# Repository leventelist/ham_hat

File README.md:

# Raspberry PI hat for radio amateurs

## History

I've been doing a lot of SOTA activations with Raspberry PI like SBCs, and there
where always issues, like RF interference, and power supply shorts. I started to
add things like galvanically decoupled audio interface, a step down power supply. It
was working, but it looked like a mess.

This piece of hardware integrates all needed equipment in one nice hat. It is designed
to put the RPI in a metallic box to further isolate from RF signals.

It was designed using [KiCad](https://www.kicad.org/).

## Applications

* HF/VHF digital modes (PSK, FT8, etc)
* HF/VHF AX.25 based modes (Packet, APRS, etc)
* CW keying
* Clock synchronization
* Position tracking

## Features

 * 3A power supply with wide input voltage range: 8 to 35V
 * Ublox MAX-8/10 GPS receiver for position and time synchronization
 * Inductive audio couplers to minimize GND loops. Up to 4kHz.
 * PWM controlled cooling fan
 * GPIO controlled PTT from the PI
 * GPIO controlled CW key from the PI
 * RTC
 * Shutdown button
 * Run LED

GPS antenna is not integrated in the device, so an external antenna connector is
mounted on the PCB.

Ufortunately, the sound card of the PI can not record audio, so an
external sound card must be used. I use
[this](https://www.axagon.eu/en/produkty/ada-17) particular device with good
results. I usually break the plastic housing, and solder a shielded cable
directly to the audio interface (J109).

The GPS is needed for APRS and time synchronization. There is an onbard RTC to have some redundancy.

## Placing variants

There are a few components that mounted or unmounted depending on particular application.

### HT radio

When this device is used with a handheld radio, that has a PTT and mic input (Like the FT-4X), mount C108 and R116. Please note that the value of R116 might vary based on the actual transceiver used.

If used with a radio that has separate input for audio and PTT, mount a 0 Ohm resistor to C108. You might also leave C108 as a capacitor (22uF), but it is not really needed.

C108 and R116 is placed on the layout that it can be mounted or replaced after everything else is mounted too. All you need is the dismount tha cooling fan.

### High bandwidth audio

If you want to have direct access to the audio interface of your radio, you can leave T101 and T102 unpopulated and short JP102 and JP103, JP104. Please note that you will loose GND separation as well.

## Mechanics

It is designed to fit on the Raspberry PI 4. Be aware, that if the heatsink on the CPU is too high, it might
conflict with the screws of the fan. If that happens, mount the heatsink 45 degrees.

### Box

A box is designed in FreeCAD using sheets of PCB. The idea is to use bare, one sided PCBs, and solder the plates from the inside. The sheets can be easily milled by a CNC machine.

There are several cutouts on the box.

In the front, you have the power inlet, and a second cutout for powering the attached LCD screen. On the right side of the front sheet, there is a cutout for the power chord to the GPS antenna, if needed.

On the right, there are anouther cutout for the audio cable.

The assembly does not include some (all) the models, hence they might violate copyright.

## Connection to the radio

The hat comes with a DB9 connector to connect up your rig. I wanted to have a screw lock
connector, and this was the best choice. The pin out looks like this.

| Signal name | Pin of the DB9 | Comment                  |
|-------------|----------------|--------------------------|
| TX audio    | 1              | Audio input of your rig  |
| KEY         | 2              | CW key of the rig        |
| PTT         | 3              | PTT input of your rig    |
| NC          | 4              | Not connected            |
| RX audio    | 5              | Audio output of your rig |
| GND         | 6              | Audio ground             |
| GND         | 7              | Audio ground             |
| GND         | 8              | Audio ground             |
| GND         | 9              | Audio ground             |

### GPIO connections

| Signal name | GPIO | Commnet |
|-------------|------|---------|
| PTT         | 12   |         |
| KEY         | 21   |         |
| DCD         | 16   |         |

## Connection to the soundcard

J105 provides connection to the soundcard.

| Signal name | Pin of J105            | Comment                          |
|-------------|------------------------|----------------------------------|
| RX audio    | 1                      | Mic input of your soundcard      |
| TX audio    | 4                      | Speaker output of your soundcard |
| GND         | 2,3                    | Audio ground                     |

## Power connection

J101 provides power connection. The maximum input voltage is 35Volts.

## GPS

Use u-blox MAX-8C/Q or MAX-M10S GNSS module. When the MAX-10 is used, don't populate R113.

Connect your passive or active GPS antenna to J104. Use 3.3V active antenna. PPS signal is provided on GPIO18.

When passive antenna is used, don't populate L102.

[Here](https://austinsnerdythings.com/2021/04/19/microsecond-accurate-ntp-with-a-raspberry-pi-and-pps-gps/) is an excellent article how to set up GPIO-PPS for ntpd.

## RTC

BQ32000 based precision RTC is provided for backup if the GPS can't provide accurate timing.

### Enable I²C on Raspberry Pi
```bash
sudo raspi-config
```
Navigate to:
```
Interfacing Options → I2C → Enable
```
Reboot the Raspberry Pi:
```bash
sudo reboot
```

### Check I²C Communication
```bash
sudo apt install i2c-tools
i2cdetect -y 1
```
You should see the RTC at **0x68**.

### Configure Linux to Use BQ32000
```bash
sudo modprobe rtc-bq32k
echo bq32000 0x68 | sudo tee /sys/class/i2c-dev/i2c-1/device/new_device

# This next one line only needed to set initial time of the RTC
# Otherwise it'll fail to read
sudo hwclock -w

# Test to read the RTC
sudo hwclock -r
```

### Make It Persistent
Edit `/boot/firmware/config.txt`:

Add the following line:
```
dtoverlay=i2c-rtc,bq32000
```
Save and reboot:
```bash
sudo reboot
```

### Disable Fake RTC (if needed)
```bash
sudo systemctl disable fake-hwclock
sudo systemctl stop fake-hwclock
```
Edit `/lib/udev/hwclock-set` and comment out:
```bash
#if [ -e /run/systemd/system ] ; then
#    exit 0
#fi
```
```bash
apt remove fake-hwclock
```

### Create a systemd service to set system clock from RTC

/etc/systemd/system/rtc-sync.service

The content of this file attached.

### Sync RTC with System Time
Set RTC from system time:
```bash
sudo hwclock -w
```
Set system time from RTC:
```bash
sudo hwclock -s
```

### Final Test
Check that the RTC retains the time after reboot:
```bash
sudo hwclock -r
```

Connect a 3V battery to BT101 for offline RTC operation.

## FAN control

PWM shall be enabled on GPIO13.

If you don't want PWM control, short JP101, and the fan will spin at full power all times.

There's a non-PWM control of the fan that works out of the box using the Raspberry PI OS.

Open raspi-config, under Performance Options, you shall select the desired temperature,
and the GPIO pin which is 13.

## Shutdown button can be connected to J106

To make it work, you have to add these lines to /boot/firmware/config,txt

```
dtoverlay=gpio-shutdown,gpio_pin=26
```

Ther's also a LED (D107 )that shines when the system is running. When it
Doesn't, it is safe to remove power from the RPI.

To make this work, add this too:

```
dtoverlay=gpio-poweroff,gpiopin=7,active_low=1
```

## Accessories

These items needed for the hat for full functionality.

All sourced from [Farnell](https://www.farnell.com/), unless othervise noted. (Sorry, I'm Hungary based.)

| Item | Source designator        | Comment |
|--------------------|------------|---------|
| RTC Battery        | 1892670    | The idea is to use heatshrink tube and some wires. |
| RTC Battery holder | 3583203    | External battery holder for CR2032 |
| Heatsink           | 1211701 or https://www.alza.hu/raspberry-pi-rb-hutoborda-d4147799.htm?o=21 ||
| Standoff           | 1466844 | It must be 12mm in length |
| Mounting screws M2.5x6 | | |
| GPS antenna        | [This](https://www.soselectronic.hu/products/2j/2j431gmp-250rg174-c20n-173902) or [this](https://www.soselectronic.hu/products/2j/2j0801b-c814g-217598) | Use 3V active antenna |
| RPI4 | 3369503 (8GB) or 3051887 (4GB) | |
| USB audio interface| [Alza](https://www.alza.hu/axagon-ada-10-mini-d1470921.htm) | Any other do the job. Check Linux driver availability. |
| Monitor| [Ebay](https://www.ebay.com/itm/353758771148?_trkparms=ispr%3D1&hash=item525daa77cc:g:jNQAAOSwnmlhhkpn&amdata=enc%3AAQAGAAACoPYe5NmHp%252B2JMhMi7yxGiTJkPrKr5t53CooMSQt2orsSd0ReTLyM7cxPnI6zs468EDJJHdbu7%252F6aAGgDwzooo3WFCnsE6WY2NN3WIFz%252BU3j%252B6nlMSYOqthKl8%252BB0CNXkHJGfWJwzf20ZY2tdDWUhthRak%252B0O%252FHuC9ltiij5XgROuZ1Yt7ahYbZ19ddFFTaniueENCnYQ1aBhlktfzWv7xNvLbyiVUMCgdXy2uwy0Qm1PC1w8PtdFCrKUjBzWedhAdATUyusA%252BLFfS8lKdAnUeEkUiXBHqDyRACtOih8HyopSoYK%252BuetmxNqJMW1yetVzEuVG55kdREQp8NK3DiaAyJ3VxZ2eCQS7MBWAslEs%252BcjPr5pLBJmvXicOdQsxG78lY3RixTMapBEXkMyMhr8CZ%252B%252BUgXa6K6nssZMYzkzb8xh6HKPf1HGRgakrkSU8iv0Jb0qSPHQQbUU%252BDDCgloGfOgyy3KP%252FVC8YO8aAXQEpuWYDxkgLVD9bG29n%252FxRT5bK91LAbViZxXBj7t3CMtKnw2FXJZp9tf8PF83bIWHzxw3%252FWPs3Q16F6D8dQrHa7%252FQKrBkX9ECfOG3J8w%252BXIaV0JdErB2c39fbNJsezMG0qO7EeJPmYWaZ4isKdigC4pZBSkcRq6YpXnZEsE%252FZbSkspYbLs5C%252F9QS17yAUWT6I9ebc9k7iy9tjIt2p2E%252F8tQXl7IEDUfLabC98laQ883Xs2%252BFUGj8w%252B%252FzyhRREPPlbA7segxjevzekGn9GUOD6kM6yCYgyqf3eMCqXgKofQIa6dmLZviddtP9L0a4A2mYfWhoSsyY%252FoBn6oAKnoTd9ymHzWRMWE5W5Act9JD6YpZT0wU8zPgG6x9%252BwGaIeGsotEsk1Bm2ccUKsKW1YO18BFmLPTsdw%253D%253D%7Cclp%3A2334524%7Ctkp%3ABFBM_P_ZwrNf)
| Keyboard | https://www.pcland.hu/genius-luxemate-100-usb-fekete-hun-billentyuzet-31300725113 | Any USB Keyboard. I use the one without keypad, for its compact size. |
| Mice | | Any USB, or BLE mice |
| SD card with Raspbian image. | | |
| uHDMI to HDMI cable | [Alza](https://www.alza.hu/vention-micro-hdmi-to-hdmi-cable-2m-black-d5891200.htm?o=1) | |
| DB9 Male connector | | To connect to your radio |
| Data connector for your radio |
| Shielded audio cable | | To connect the soundcard to the hat, and for the DB9 connector |

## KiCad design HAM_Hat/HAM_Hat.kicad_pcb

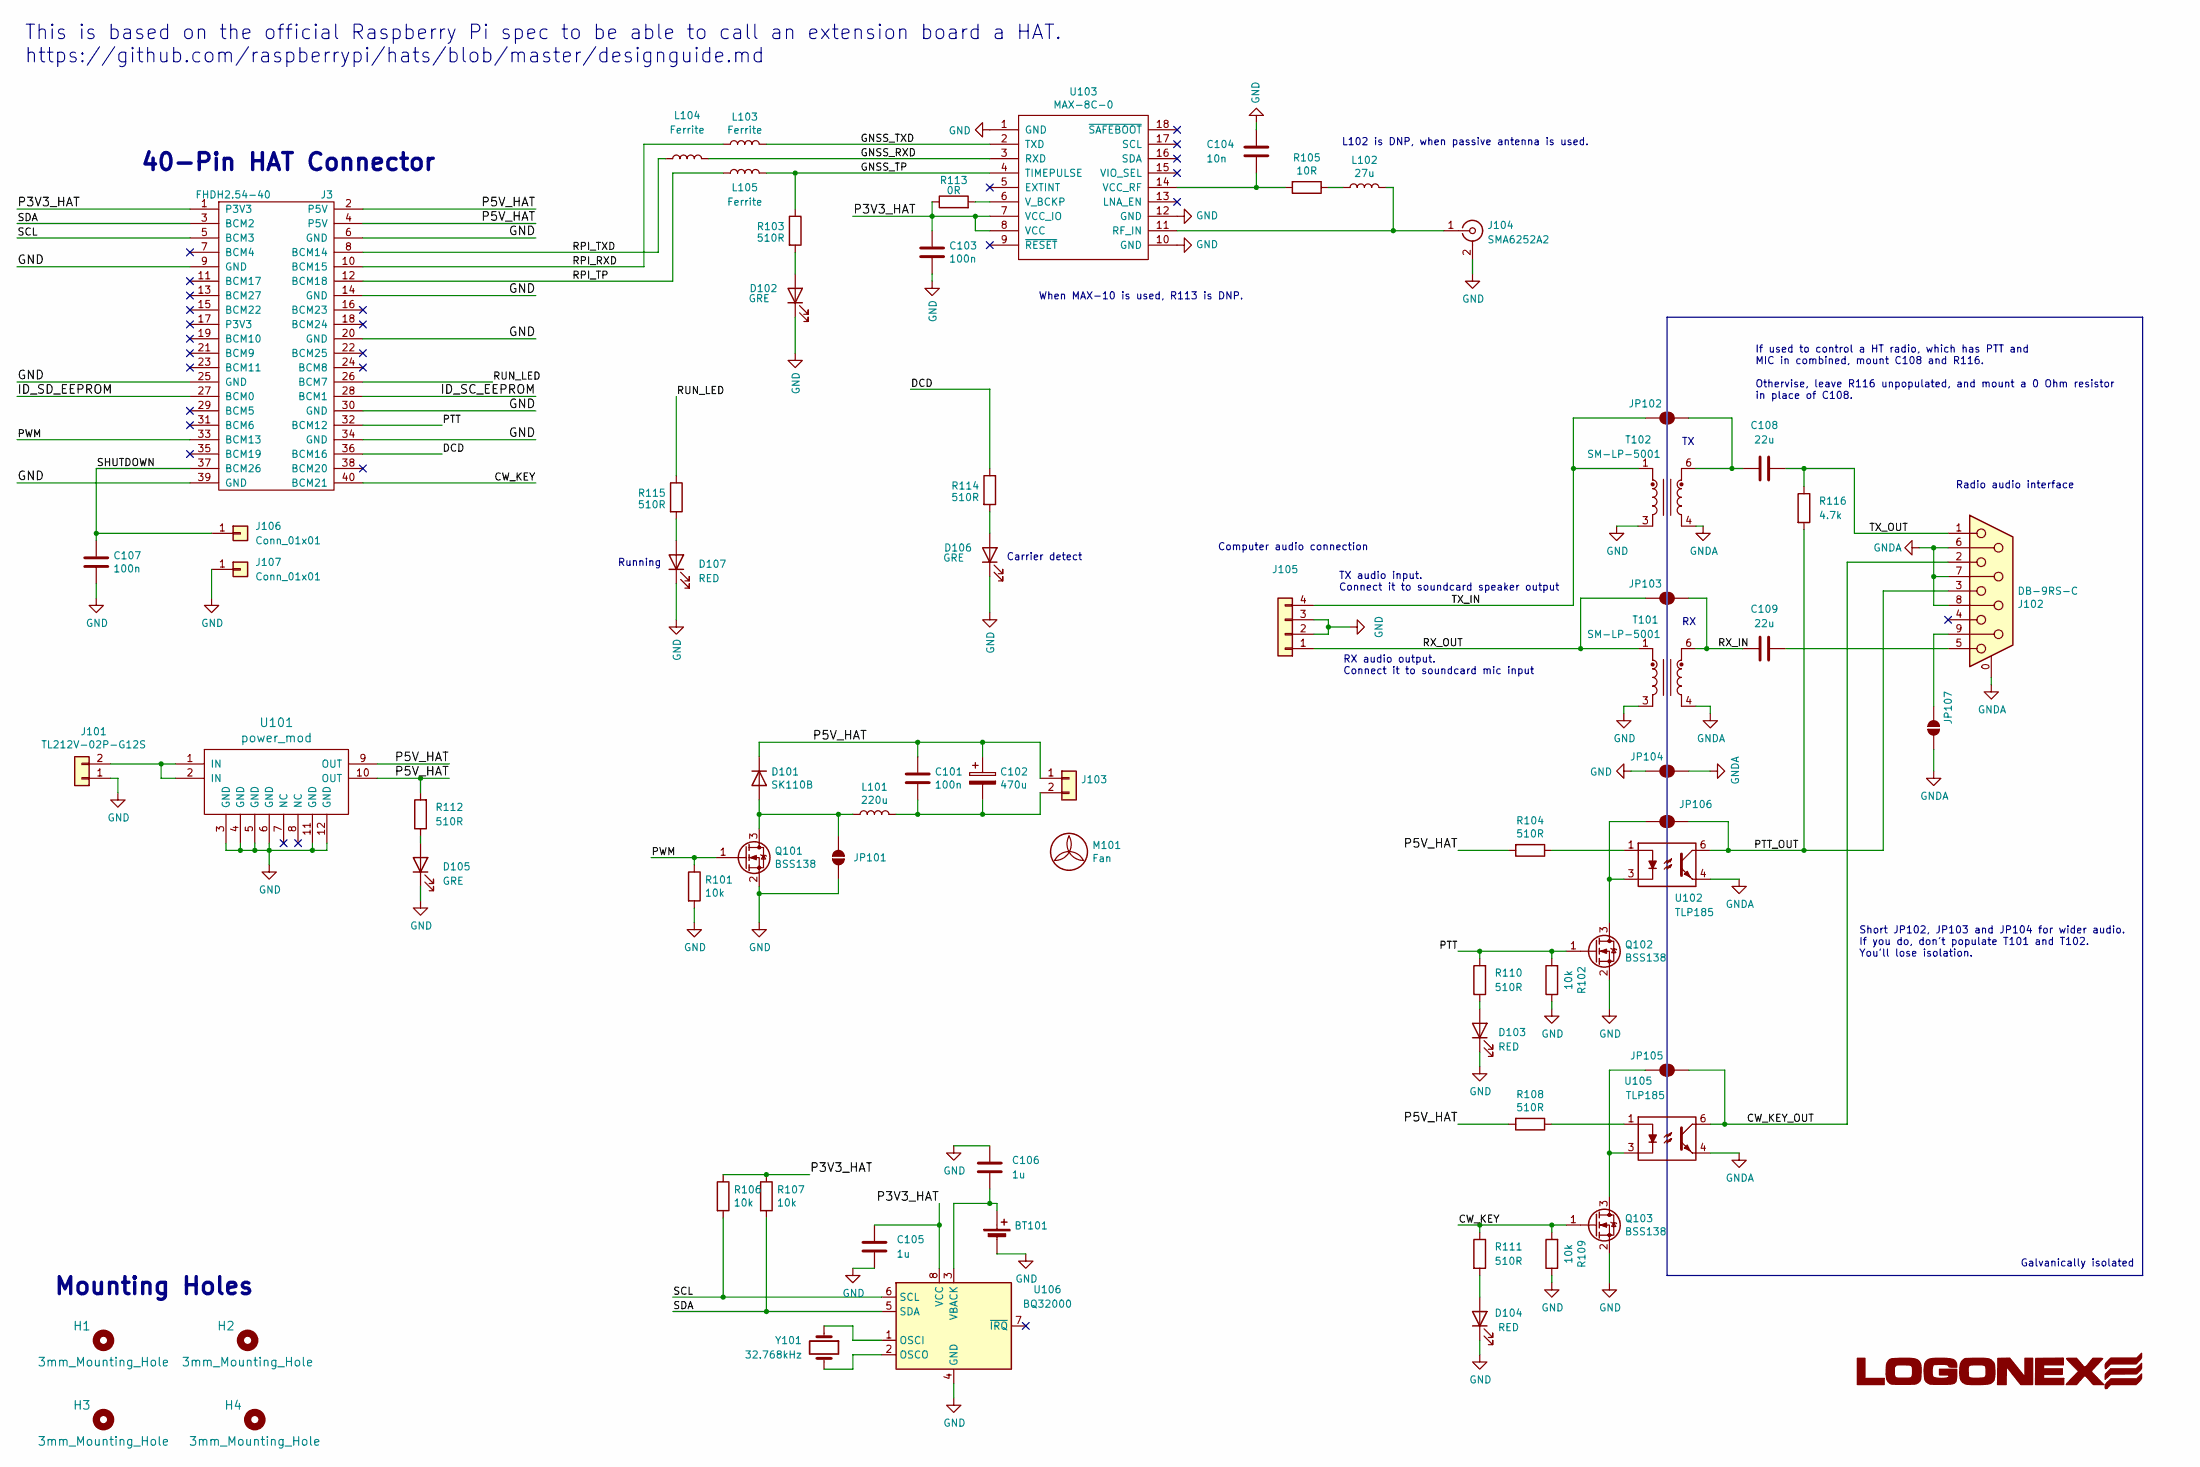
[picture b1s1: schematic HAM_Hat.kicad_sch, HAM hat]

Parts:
BT101: PinHeader_2x01_P2.54mm_Vertical
C101, C103, C107: 100n; C_0603_1608Metric
C102: 470u; CP_Radial_D10.0mm_P5.00mm
C104: 10n; C_0603_1608Metric
C105, C106: 1u; C_0603_1608Metric
C108, C109: 22u; C_1206_3216Metric
D101: SK110B; D_SMB
D102, D105, D106: GRE; LED_0603_1608Metric
D103, D104, D107: RED; LED_0603_1608Metric
H1, H2, H3, H4: 3mm_Mounting_Hole; l_MountingHole_Clear_2.75mm_M2.5
J3: FHDH2.54-40; PinSocket_2x20_P2.54mm_Vertical
J101: TL212V-02P-G12S; TerminalBlock-2-5.0_1x02_P5.0mm_Horizontal
J102: DB-9RS-C; DSUB-9_Female_Horizontal_P2.77x2.84mm_EdgePinOffset7.70mm_H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
J103: PinHeader_1x02_P2.54mm_Vertical
J104: SMA6252A2; SMA_angled
J105: PinHeader_1x04_P2.54mm_Vertical
J106, J107: Conn_01x01; SolderWirePad_1x01_SMD_2x5mm
JP101, JP102, JP103, JP104, JP105, JP106, JP107: SolderJumper_2_Open; SolderJumper-2_P1.3mm_Open_RoundedPad1.0x1.5mm
L101: 220u; IND_PCD0504
L102: 27u; L_0603_1608Metric
L103, L104, L105: Ferrite; R_0805_2012Metric
M101: Fan; 25x25
Q101, Q102, Q103: BSS138; SOT-23
R101, R102, R106, R107, R109: 10k; R_0603_1608Metric
R103, R104, R108, R110, R111, R112, R114, R115: 510R; R_0603_1608Metric
R105: 10R; R_0603_1608Metric
R113: 0R; R_0603_1608Metric
R116: 4.7k; R_0603_1608Metric
T101, T102: SM-LP-5001; SM_LP_5001
U101: power_mod; power_mod3A
U102, U105: TLP185; 11-4M1S
U103: MAX-8C-0; MAX8
U106: BQ32000; SOIC-8_3.9x4.9mm_P1.27mm
Y101: 32.768kHz; Crystal_DS26_D2.0mm_L6.0mm_Vertical

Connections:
/CW_KEY: J3.40 (BCM21), Q103.1 (G), R109.2, R111.1
/CW_KEY_OUT: J102.2, JP105.2 (B), U105.6
/DCD: J3.36 (BCM16), R114.1
/GNSS_RXD: L104.2, U103.3 (RXD)
/GNSS_TP: L105.2, R103.1, U103.4 (TIMEPULSE)
/GNSS_TXD: L103.2, U103.2 (TXD)
/ID_SC_EEPROM: J3.28 (BCM1)
/ID_SD_EEPROM: J3.27 (BCM0)
/P3V3_HAT: C103.1, C105.1, J3.1 (P3V3), R106.1, R107.1, R113.1, U103.7 (VCC_IO), U103.8 (VCC), U106.8 (VCC)
/P5V_HAT: C101.1, C102.1, D101.1 (K), J3.2 (P5V), J3.4 (P5V), J103.1, R104.2, R108.2, R112.2, U101.9 (OUT), U101.10 (OUT)
/PTT: J3.32 (BCM12), Q102.1 (G), R102.2, R110.2
/PTT_OUT: J102.3, JP106.2 (B), R116.2, U102.6
/PWM: J3.33 (BCM13), Q101.1 (G), R101.1
/RPI_RXD: J3.10 (BCM15), L103.1
/RPI_TP: J3.12 (BCM18), L105.1
/RPI_TXD: J3.8 (BCM14), L104.1
/RUN_LED: J3.26 (BCM7), R115.1
/RX_IN: C109.2, JP103.2 (B), T101.6
/RX_OUT: J105.1, JP103.1 (A), T101.1
/SCL: J3.5 (BCM3), R106.2, U106.6 (SCL)
/SDA: J3.3 (BCM2), R107.2, U106.5 (SDA)
/SHUTDOWN: C107.1, J3.37 (BCM26), J106.1
/TX_IN: J105.4, JP102.1 (A), T102.1
/TX_OUT: C108.2, J102.1, R116.1
GND: BT101.2 (-), C103.2, C104.1, C105.2, C106.1, C107.2, D102.1 (K), D103.1 (K), D104.1 (K), D105.1 (K), D106.1 (K), D107.1 (K), J3.6 (GND), J3.9 (GND), J3.14 (GND), J3.20 (GND), J3.25 (GND), J3.30 (GND), J3.34 (GND), J3.39 (GND), J101.1, J104.2 (Ext), J105.2, J105.3, J107.1, JP101.2 (B), JP104.1 (A), Q101.2 (S), Q102.2 (S), Q103.2 (S), R101.2, R102.1, R109.1, T101.3, T102.3, U101.3 (GND), U101.4 (GND), U101.5 (GND), U101.6 (GND), U101.11 (GND), U101.12 (GND), U103.1 (GND), U103.10 (GND), U103.12 (GND), U106.4 (GND)
GNDA: J102.0 (PAD), J102.6, J102.7, J102.8, JP104.2 (B), JP107.2 (B), T101.4, T102.4, U102.4, U105.4
unnamed: BT101.1 (+), C106.2, U106.3 (VBACK)
unnamed: C109.1, J102.5
unnamed: D101.2 (A), JP101.1 (A), L101.1, Q101.3 (D)
unnamed: D102.2 (A), R103.2
unnamed: D103.2 (A), R110.1
unnamed: D104.2 (A), R111.2
unnamed: D105.2 (A), R112.1
unnamed: D106.2 (A), R114.2
unnamed: D107.2 (A), R115.2
unnamed: J101.2, U101.1 (IN), U101.2 (IN)
unnamed: C101.2, C102.2, J103.2, L101.2
unnamed: J104.1 (In), L102.2, U103.11 (RF_IN)
unnamed: C108.1, JP102.2 (B), T102.6
unnamed: JP105.1 (A), Q103.3 (D), U105.3
unnamed: JP106.1 (A), Q102.3 (D), U102.3
unnamed: J102.9, JP107.1 (A)
unnamed: L102.1, R105.1
unnamed: R104.1, U102.1
unnamed: R108.1, U105.1
unnamed: C104.2, R105.2, U103.14 (VCC_RF)
unnamed: R113.2, U103.6 (V_BCKP)
unnamed: U106.1 (OSCI), Y101.1
unnamed: U106.2 (OSCO), Y101.2

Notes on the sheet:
Carrier detect
When MAX-10 is used, R113 is DNP.
This is based on the official Raspberry Pi spec to be able to call an extension board a HAT. https://github.com/raspberrypi/hats/blob/master/designguide.md
Radio audio interface
If used to control a HT radio, which has PTT and MIC in combined, mount C108 and R116. Othervise, leave R116 unpopulated, and mount a 0 Ohm resistor in place of C108.
Galvanically isolated
L102 is DNP, when passive antenna is used.
Short JP102, JP103 and JP104 for wider audio. If you do, don't populate T101 and T102. You'll lose isolation.
Mounting Holes
RX audio output. Connect it to soundcard mic input
40-Pin HAT Connector
TX audio input. Connect it to soundcard speaker output
Computer audio connection
Running

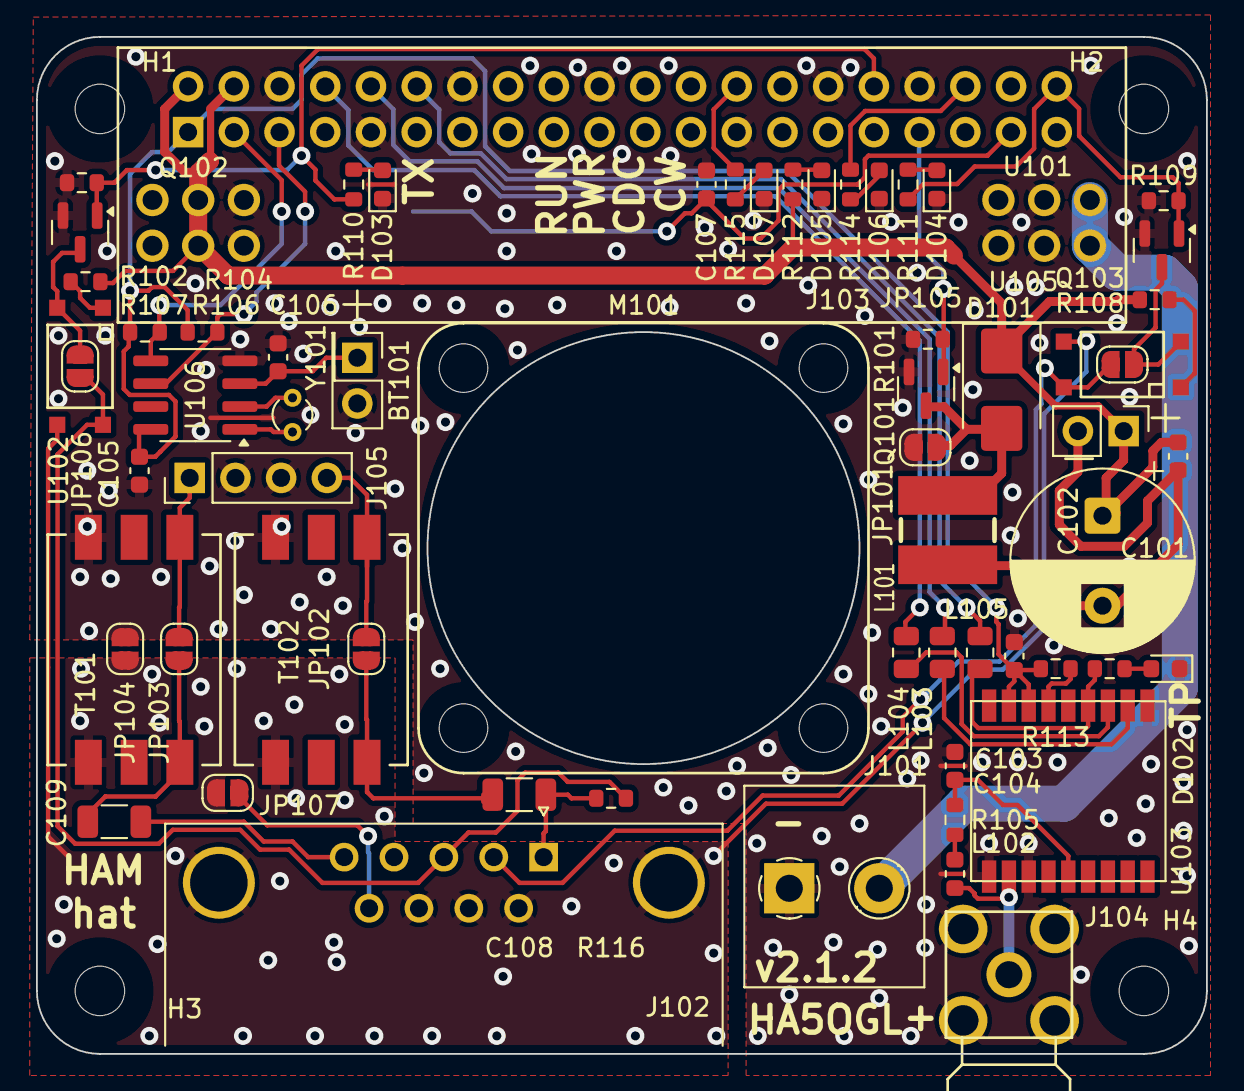
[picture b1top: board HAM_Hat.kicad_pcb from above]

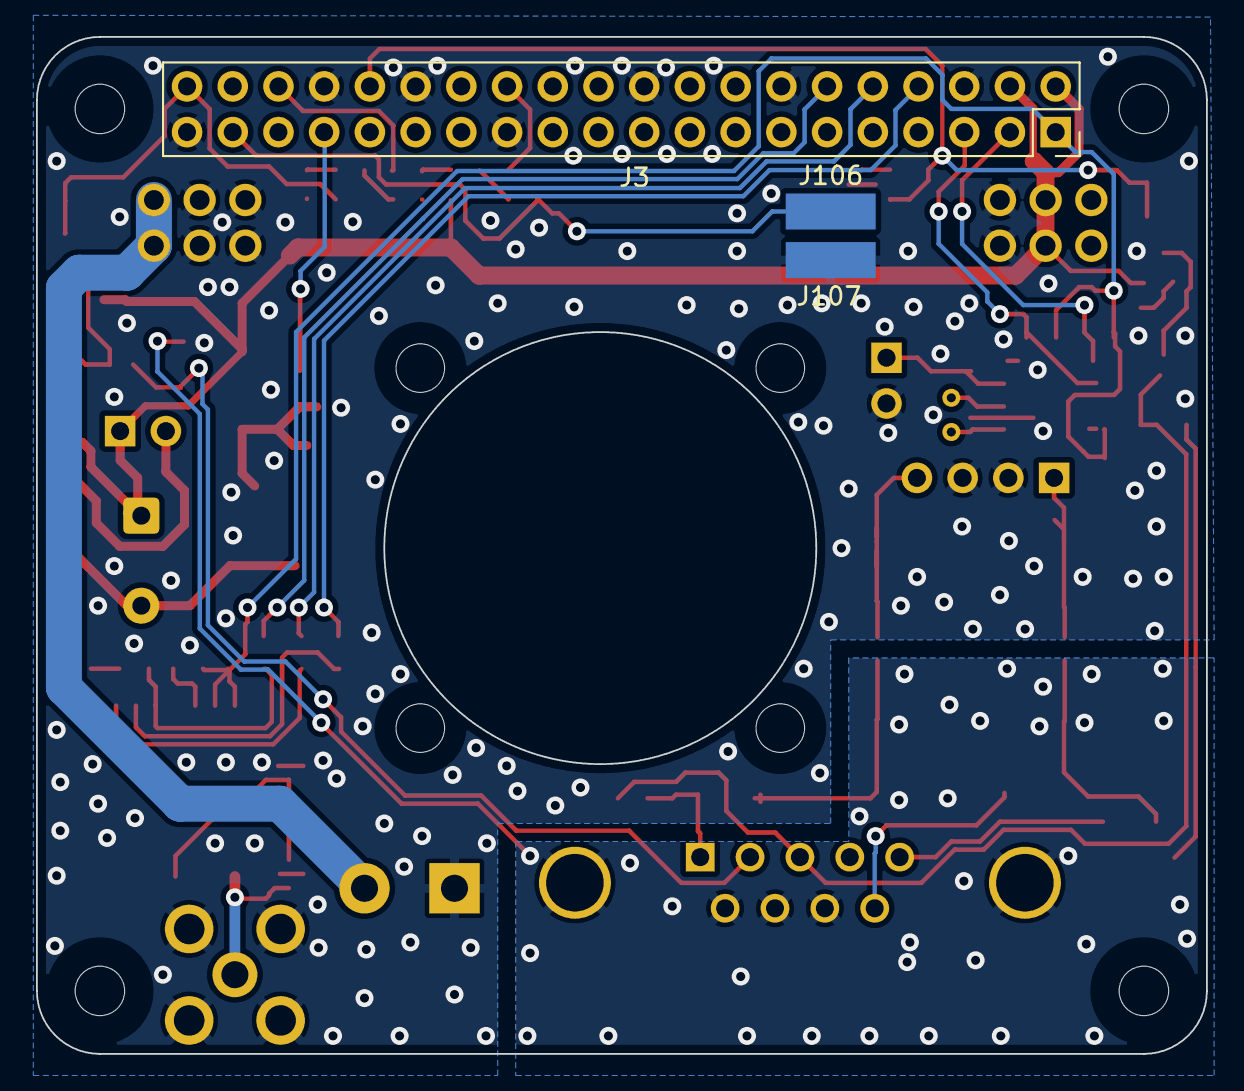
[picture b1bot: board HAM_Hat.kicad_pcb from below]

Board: 2 copper layers, 65.0 x 56.5 mm, 69 parts (3 on the bottom side), 47 nets.

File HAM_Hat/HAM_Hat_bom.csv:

"Source:","/home/lev/git/ham/ham_hat/HAM_Hat/HAM_Hat.sch"
"Date:","Fri 03 Dec 2021 04:00:20 PM CET"
"Tool:","Eeschema (5.1.12)"
"Generator:","/home/lev/git/library/software/kicad_utils/bomer2.py"
"Component Count:","41"
"Refs","id","Qty","Value","Value2","Value3","Device description","Cmp name","Footprint","CAD description","Ordering code","Supplier","Subtotal","Total"
"C101,C103","145","2","100n","16V","10%","ceramic capacitor","C","Capacitor_SMD:C_0603_1608Metric","Unpolarized capacitor","82-02-51","Lomex kft.","1.58",""
"C102","30","1","470u","25V","20%","","CP","Capacitor_THT:CP_Radial_D10.0mm_P5.00mm","Polarized capacitor","12-18-79","Lomex kft.","15.6",""
"C104","608","1","10n","50V","10%","","C","Capacitor_SMD:C_0603_1608Metric","Unpolarized capacitor","82-06-12","Lomex kft.","0.38",""
"D101","144","1","SK110B","1A","100V","Schottky rectifier","D","Diode_SMD:D_SMB","Diode","83-01-14","Lomex kft.","18.3",""
"D102","147","1","GRE","","","green led","LED","LED_SMD:LED_0603_1608Metric","Light emitting diode","95-01-08","Lomex kft.","8.0",""
"J3","757","1","FHDH2.54-40","3A","1000V","","PI40HAT","Connector_PinSocket_2.54mm:PinSocket_2x20_P2.54mm_Vertical","OX40 Raspberry Pi HAT Connector","43-06-67","Lomex kft.","87.0",""
"J101","627","1","TL212V-02P-G12S","","","","Conn_01x02","l_connector:TerminalBlock-2-5.0_1x02_P5.0mm_Horizontal","Generic connector, single row, 01x02, script generated (kicad-library-utils/schlib/autogen/connector/)","43-29-96","Lomex kft.","36.1",""
"J102","330","1","DB-9RS-C","","","","DB9_Female_MountingHoles","Connector_Dsub:DSUB-9_Female_Horizontal_P2.77x2.84mm_EdgePinOffset4.94mm_Housed_MountingHolesOffset7.48mm","9-pin female D-SUB connector, Mounting Hole","43-00-45","Lomex kft.","55.4",""
"J103","320","1","NCW254-02S","","","","Conn_01x02","Connector_Molex:Molex_KK-254_AE-6410-02A_1x02_P2.54mm_Vertical","Generic connector, single row, 01x02, script generated (kicad-library-utils/schlib/autogen/connector/)","43-08-95","Lomex kft.","1.98",""
"J104","658","1","SMA6252A2","","","90deg SMA Amphenol","Conn_Coaxial","l_rf:SMA_angled","coaxial connector (BNC, SMA, SMB, SMC, Cinch/RCA, ...)","471-SMARACONNECTOR ","Mouser","597.0",""
"L101","563","1","220u","350mA","","PCD0504-221","L","l_SM_inductors:IND_PCD0504","Inductor","93-02-84","Lomex kft.","20.0",""
"L102","756","1","27u","300mA","1750MHz","","L","Inductor_SMD:L_0603_1608Metric","Inductor","93-03-93","Lomex kft.","9.32",""
"L103,L104","351","2","Ferrite","1000R","100MHz","","L","Resistor_SMD:R_0805_2012Metric","Inductor","93-03-14","Lomex kft.","3.8",""
"M101","759","1","Fan","5V","","","Fan","l_fan:25x25","Fan","CY 2510/05V2-A99","HQ Elektronika","1826.0",""
"Q101,Q102","78","2","BSS138","0.22A","50V","small signal nmos","Q_NMOS_GSD","Package_TO_SOT_SMD:SOT-23","N-MOSFET transistor, gate/source/drain","86-02-70","Lomex kft.","15.8",""
"R101,R102","183","2","10k","0.1W","1%","","R","Resistor_SMD:R_0603_1608Metric","Resistor","80-11-68","Lomex kft.","0.86",""
"R103,R104","390","2","510R","0.1W","1%","","R","Resistor_SMD:R_0603_1608Metric","Resistor","80-04-35","Lomex kft.","0.66",""
"R105","755","1","10R","0.1W","1%","","R","Resistor_SMD:R_0603_1608Metric","Resistor","80-11-87","Lomex kft.","0.28",""
"RV101,RV102","466","2","10k","25t","","","R_POT","Potentiometer_THT:Potentiometer_Bourns_3296W_Vertical","Potentiometer","05-05-89","Lomex kft.","122.0",""
"T101,T102","738","2","SM-LP-5001","1:1","","","PA2006NL","l_transformer:SM_LP_5001","SMT Gate Drive Transformer, 1:1","55-01-09","Lomex kft.","968.0",""
"U102","643","1","TLP185","3.75kV","50%","optocoupler","TLP185","l_optocoupler:11-4M1S","","84-00-94","Lomex kft.","34.339999999999996",""
"U103","758","1","MAX-8C-0","2.7V to 3.6V","","","MAX8","l_rf:MAX8","","377-MAX-8C-0 ","Mouser","6781.0",""
"","","","","","","","","","","","","","10603.400000000001"

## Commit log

2021-11-30 Some progress on the layout
2021-12-01 0 unconnect
2021-12-02 Release candidate
2021-12-02 Title block
2021-12-02 Bump version: 0.0.0 → 1.0.0
2021-12-02 Add README.md
2021-12-02 Add spaces to # chars.
2021-12-02 Update on the readme
2021-12-02 Add image
2021-12-03 Some minor changes
2021-12-03 Documentation update
2021-12-03 Add BOM
2021-12-03 DE9 pinout change
2021-12-04 Some more ideas. Thanks John WB2OSZ!
2021-12-04 Schematic update
2021-12-04 Bump version: 1.0.0 → 1.0.1
2021-12-04 Fix outline
2021-12-04 Fix mechanical collisions with the PI
2021-12-04 Bump version: 1.0.1 → 1.0.2
2021-12-04 Fix typos
2021-12-04 Add some notes about the fan.
2021-12-04 Other documetation fixes
2021-12-04 Some optiomization
2021-12-04 Bump version: 1.0.2 → 1.0.3
2021-12-04 Update image
2021-12-04 New assembly
2021-12-04 More fixes
2021-12-05 Add RTC
    Also add header socket for audio connection.
2021-12-05 Add RTC
    Audio connection replaced by a header socket.
2021-12-05 Bump version: 1.0.3 → 1.0.4
2021-12-05 Update the exports.
2021-12-06 Add accessories notes.
2021-12-06 Some fixes
2021-12-06 Add some ideas
2021-12-07 Update accessory list
2021-12-08 Add 4pin header into BoM
2021-12-08 Accessories moved to README.md
2021-12-08 Typo fixes
2021-12-08 Some more info to accessories
2021-12-08 Even more items
2023-01-16 Migrate to KiCad v7
2023-01-16 Some leftover from the migration
2023-01-20 Update the readme
2023-01-20 Typo fix
2023-01-20 3D models added
2023-01-20 Replace the DB9 connector
2023-01-21 Add CW keying function
2023-01-22 Some progress on the CW keying support
2023-01-23 CW keying added
2023-01-23 Mounting holes changed
2023-01-23 Update documentation
2023-01-23 Bump version: 1.0.4 → 1.1.0
2023-04-05 KiCad file format update
2023-04-05 Connect more GND to the connector
2023-04-05 Add 0.5mm edge clearence to copper.
2023-04-05 Minor issues fixed
2024-03-29 Migration to KiCad v8.0.1
2024-08-29 Remove the potmeters. Add more robust connector
2024-08-29 New schematic
2024-12-29 Add LEDs to CW and PTT lines
    Rotate the GPS module
2024-12-31 Add u.fl connector instead of the SMA
2025-01-02 Add power LED
2025-01-02 Update the docs
2025-01-02 Bump version: 1.1.0 → 2.0.0
2025-01-02 Add new image
2025-01-11 U.FL connector replace
    Migration to Kicad v9
2025-02-01 Minor changes
2025-02-01 Change the RTC to some cheeper one
2025-04-13 PS footprint update
2025-04-13 Version number moved
2025-04-13 Move texts
2025-04-13 Bump version: 2.0.0 → 2.0.1
2025-04-28 Add DCD LED
2025-04-28 Bump version: 2.0.1 → 2.1.0
2025-04-30 Add todo file
2025-04-30 LED moved
2025-04-30 Alternative LED positions
2025-04-30 Bump version: 2.1.0 → 2.1.1
2025-05-09 Add shutdown switch interface
2025-05-10 Add run LED
2025-05-10 Add Shutdown button and Run LED doc
2025-05-10 Remove schematic plot
2025-05-10 PCB: FIX DRC warnings. Also updated footprints
2025-05-19 Rearrange GPS. Possibly better performance
2025-05-19 Bump version: 2.1.1 → 2.1.2
2025-06-18 Image update
2025-07-01 Some change on the assembly
2025-07-01 Add box
    This needs to be redone.
2025-07-02 Add assembly
2025-07-03 Modify cutout for power chord
2025-07-03 Add CNC files
2025-07-08 Add battery holder
2025-07-08 Add cutout for audio cable
    This makes the model broken.
2025-07-08 Add documentation for the box
2025-07-08 Add the assembly rendering
2025-07-18 Use external GNSS
2025-08-02 Fix RTC description
2025-08-02 Fix RTC description
    (cherry picked from commit 0d283c59cc2733d0173354e308218f616516c40f)
2025-08-03 Add shutdown button to the box
2025-08-04 Replace the 2mm pitch connector to 2.54mm pitch
    This is not really a connector, rather then a pads to
    solder wires.
2025-08-04 Update DXF exports
2025-08-04 Explode objects
2025-08-04 Removed redundant lines
2025-08-04 NGCs generated.
2025-08-10 Add HT radio option
2025-08-13 Fix some issues
2025-08-15 Move shutdown connector
2025-08-20 Some minor fix of the documentation
2025-08-20 Add table
2025-09-27 Add DC decoupling capactiors
2026-06-29 RTC setup
